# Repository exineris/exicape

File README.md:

# Exi Cape

## 1.はじめに

[BeagleBoard](https://beagleboard.org/)に、産業機器を接続するためのインターフェースボード([CAPE](https://beagleboard.org/capes))です。

**Note**

Please import this library before using this repository.
<https://github.com/trihome/KiCad_MyLibrary>

## 2.仕様

[回路図](./doc/ExiCape.pdf)

|機能|仕様|補足|
|:--|:--|:--|
|出力|4ch|非絶縁。シンク（NPN）・ソース（PNP）駆動切り替え可能。各chの動作確認LEDあり。|
|入力|4ch|〃|
|AD変換|10bit 2ch|非絶縁・入力保護のダイオード付き|
|暗号化|ATECC508A/608A|[NervesKey](https://github.com/nerves-hub/nerves_key)の接続に対応|
|外部操作スイッチ|Power, Reset, μBoot||
|外部UART端子|あり x 1|Beagle Bone GreenのUARTに直結|
|電源|5V系/24V系は個別に供給|ポリスイッチ（過電流防止）あり|

## 3.License

This is under [CC-BY-SA](https://creativecommons.org/licenses/by-sa/4.0/).

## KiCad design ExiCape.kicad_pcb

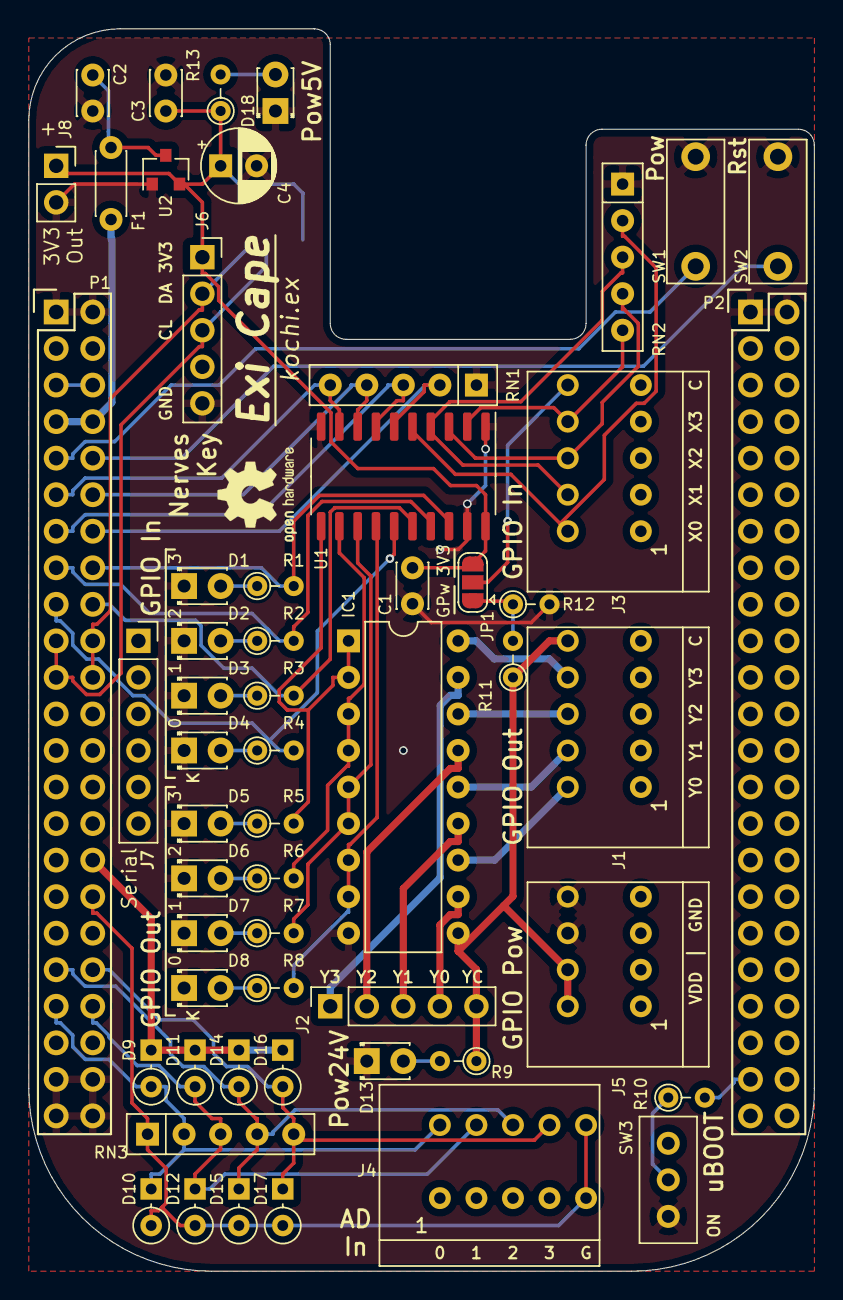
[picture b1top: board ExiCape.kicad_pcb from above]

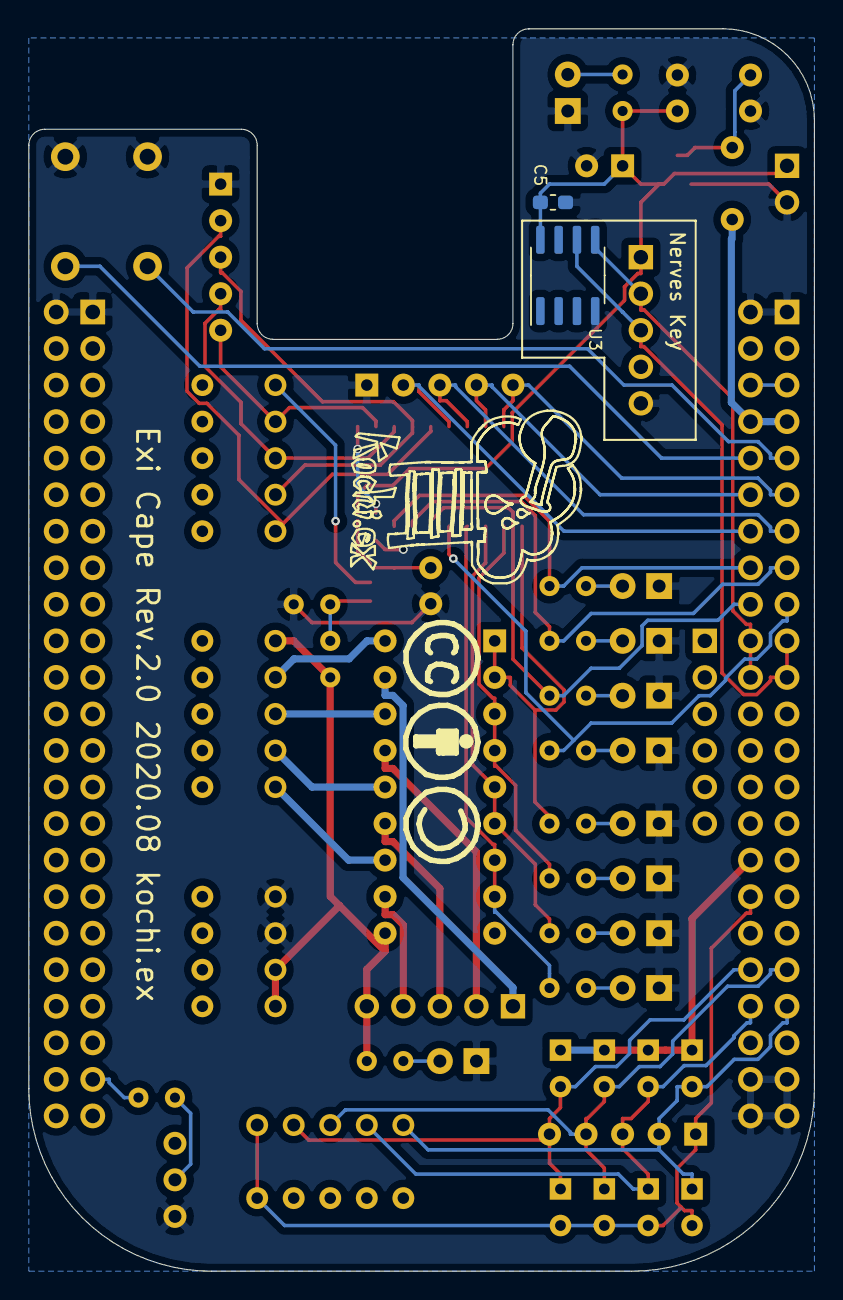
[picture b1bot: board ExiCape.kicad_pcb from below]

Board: 2 copper layers, 54.6 x 86.4 mm, 60 parts (2 on the bottom side), 54 nets.

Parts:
C1: 0.1u; C_Disc_D3.0mm_W2.0mm_P2.50mm
C2, C3: 1u; C_Disc_D3.0mm_W2.0mm_P2.50mm
C4: 100u; CP_Radial_D5.0mm_P2.50mm
C5: 0.1u; C_0603_1608Metric_Pad1.05x0.95mm_HandSolder
D1, D2, D3, D4: LED-G; LED_D1.8mm_W3.3mm_H2.4mm
D5, D6, D7, D8: LED-Y; LED_D1.8mm_W3.3mm_H2.4mm
D9, D10, D11, D12, D14, D15, D16, D17: 1N4148; D_DO-34_SOD68_P2.54mm_Vertical_KathodeUp
D13, D18: LED; LED_D1.8mm_W3.3mm_H2.4mm
F1: Polyfuse; C_Disc_D4.3mm_W1.9mm_P5.00mm
H1: MountingHole; OSHW-Logo2_7.3x6mm_SilkScreen
H2: MountingHole; CC-BY-SA
IC1: TBD62083APG; DIP-18_W7.62mm
J1: GPIO_OUT1; Terminal_TB401-1-5-E
J2: GPIO_OUT2; PinSocket_1x05_P2.54mm_Vertical
J3: GPIO_IN1; Terminal_TB401-1-5-E
J4: AD_IN1; Terminal_TB401-1-5-E
J5: GPIO_POW; Terminal_TB401-1-4-E
J6: NervesKey; PinSocket_1x05_P2.54mm_Vertical
J7: Serial Debug; PinSocket_1x06_P2.54mm_Vertical
J8: +3.3 Out; PinSocket_1x02_P2.54mm_Vertical
JP1: Sel GPow/3V3; SolderJumper-3_P1.3mm_Open_RoundedPad1.0x1.5mm
P1, P2: BeagleBone_Black_Header; Socket_BeagleBone_Black
R1, R2, R3, R4: 2k; R_Axial_DIN0204_L3.6mm_D1.6mm_P2.54mm_Vertical
R5, R6, R7, R8, R9, R11, R13: 1k; R_Axial_DIN0204_L3.6mm_D1.6mm_P2.54mm_Vertical
R10: 100; R_Axial_DIN0204_L3.6mm_D1.6mm_P2.54mm_Vertical
R12: 150; R_Axial_DIN0204_L3.6mm_D1.6mm_P2.54mm_Vertical
RN1, RN2: 10k; R_Array_SIP5
RN3: 100k; R_Array_SIP5
SW1: Power; TactileSwitch_TVBP06-B043C
SW2: Reset; TactileSwitch_TVBP06-B043C
SW3: uSD_BOOT; Switch_SS12D01G4
U1: TC74HC541AP; SO-20_5.3x12.6mm_P1.27mm
U2: MCP1703A-3302_SOT23; SOT-23
U3: ATECC608A-SSHDA; SOIC-8_3.9x4.9mm_P1.27mm

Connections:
+3V3: C1.1, C3.1, C4.1, C5.1, J6.1, J8.1, JP1.3, R13.1, U1.20, U2.2, U3.8
+5V: P1.5, P1.6
/AIN0: D9.2, D10.1, J4.2, P1.39, RN3.2
/AIN1: D11.2, D12.1, J4.4, P1.40, RN3.3
/AIN2: D14.2, D15.1, J4.6, P1.37, RN3.4
/AIN3: D16.2, D17.1, J4.8, P1.38, RN3.5
/GPIO_04: P1.18, R3.2, U1.16
/GPIO_05: P1.17, R4.2, U1.15
/GPIO_30: P1.11, RN1.5, U1.9
/GPIO_31: P1.13, RN1.3, U1.7
/GPIO_48: P1.15, R2.2, U1.17
/GPIO_50P: P1.14, RN1.2, U1.6
/GPIO_51P: P1.16, R1.2, U1.18
/GPIO_60: P1.12, RN1.4, U1.8
/I2C2_SCL: J6.3, P1.19, P1.21, U3.6
/I2C2_SDA: J6.2, P1.20, P1.22, U3.5
/PY0-1: IC1.12, J1.2
/PY0-2: IC1.11, J2.4
/PY1-1: IC1.14, J1.4
/PY1-2: IC1.13, J2.3
/PY2-1: IC1.16, J1.6
/PY2-2: IC1.15, J2.2
/PY3-1: IC1.18, J1.8
/PY3-2: IC1.17, J2.1
/PowX: J3.10, JP1.2
/X0: J3.2, RN2.2, U1.5
/X1: J3.4, RN2.3, U1.4
/X2: J3.6, RN2.4, U1.3
/X3: J3.8, RN2.5, U1.2
/Y0: IC1.7, IC1.8, R8.2, U1.14
/Y1: IC1.5, IC1.6, R7.2, U1.13
/Y2: IC1.3, IC1.4, R6.2, U1.12
/Y3: IC1.1, IC1.2, R5.2, U1.11
GNDA_ADC: D10.2, D12.2, D15.2, D17.2, J4.9, J4.10, P1.34, RN3.1
GNDD: C1.2, C2.2, C3.2, C4.2, C5.2, D1.1, D2.1, D3.1, D4.1, D5.1, D6.1, D7.1, D8.1, D13.1, D18.1, IC1.9, J5.6, J5.8, J6.5, J8.2, P1.1, P1.2, P1.43, P1.44, P1.45, P1.46, P2.1, P2.2, R12.2, RN1.1, RN2.1, SW1.2, SW2.2, SW3.3, U1.1, U1.10, U1.19, U2.1, U3.4
unnamed: C2.1, F1.1, U2.3
unnamed: D1.2, R1.1
unnamed: D2.2, R2.1
unnamed: D3.2, R3.1
unnamed: D4.2, R4.1
unnamed: D5.2, R5.1
unnamed: D6.2, R6.1
unnamed: D7.2, R7.1
unnamed: D8.2, R8.1
unnamed: D13.2, R9.2
unnamed: D18.2, R13.2
unnamed: JP1.1, R11.2, R12.1
unnamed: R10.1, SW3.2
PWR_BUT: P1.9, SW1.1
SYS_5V: F1.2, P1.7, P1.8
SYS_RESETN: P1.10, SW2.1
VDDF: IC1.10, J1.10, J2.5, J5.2, J5.4, R9.1, R11.1
VDD_ADC: D9.1, D11.1, D14.1, D16.1, P1.32
uSD_BOOT: P2.43, R10.2

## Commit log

2020-12-22 Add files
2020-12-23 Update README.md
    append crypt chip 608A

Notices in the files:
parts and their libraries:
Creative Commons Licence
